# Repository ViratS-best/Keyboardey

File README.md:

Link: https://cad.onshape.com/documents/37fd5a85f79ebe20a6029276/w/db3c2ffc712adf7ef06de7c5/e/88f673a97a289337726580ef?renderMode=0&uiState=6ad8d7fe5b5abcf9bb015cb8

# Keyboardey

A weird keyboard CAD & Hardware design created for Half-Life.

## Overview

Keyboardey is a weird, funky, custom-designed keypad layout built entirely from scratch. This project was my second time ever using CAD, making it quite a large learning curve in learning how to design mechanical parts, shape custom keys, etc. I also designed a PCB to go along with this project!

# Cad

I also had to create a custom cutout extrude to position keys correctly!

PCB and Case on Onshape (This was when I didn't know that I would actually have to change key chapes, and cutout shape):

## Project Structure

```text
|── README.md
|── KEYBOARDEY.kicad__pcb
|── KEYBOARDEY.kicad__prl
|── KEYBOARDEY.kicad__pro
|── KEYBOARDEY.kicad__sch
|── Keyboardey.step
```

# PCB

I decided to not use a module microcontroller but rather build one myself:

Then I added the keyboard matrix:

Finished MCU schematic:

Routing & Placement:

# BoM

| Component / Service  | Description                           | Cost    |
| -------------------- | ------------------------------------- | ------- |
| PCB & Assembly       | Manufactured and assembled via JLCPCB | $29.08  |
| 3D Printing          | Case and custom keycaps (estimated)   | ~$4.25 |
| Kalih Choc Switches  | Low profile key switches for keys     | $8  |
| Shipping             | Shipping and handling                 | $31.55  |
| Total Estimated Cost |                                       | ~$72.88 |

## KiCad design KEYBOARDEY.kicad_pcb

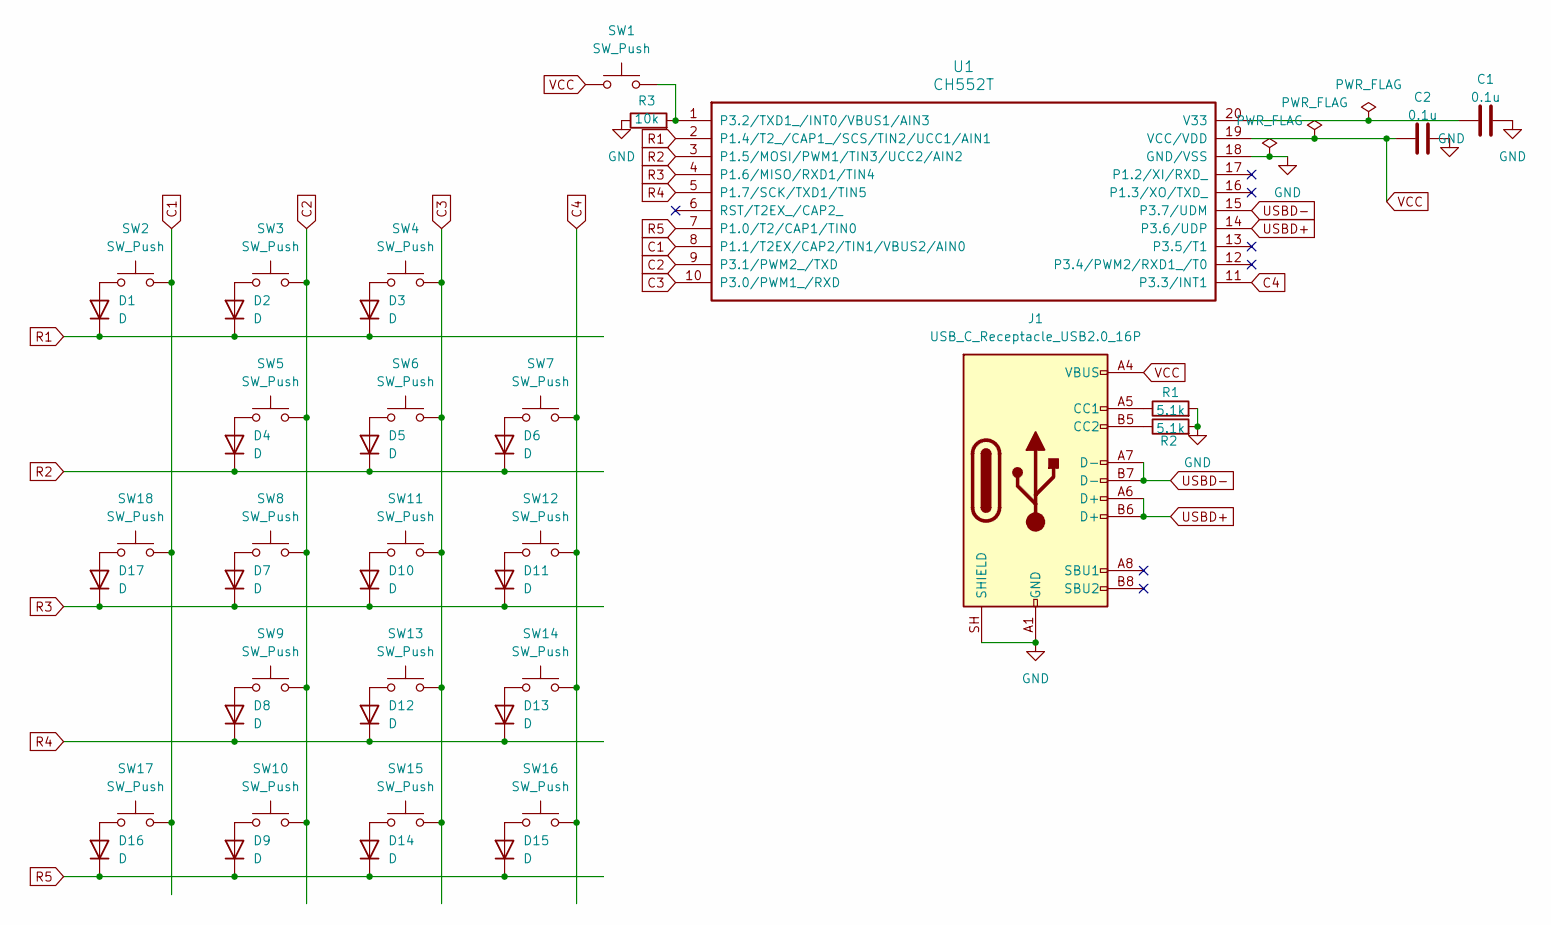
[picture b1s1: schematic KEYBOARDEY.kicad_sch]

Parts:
C1, C2: 0.1u; C_0402_1005Metric
D1, D2, D3, D4, D5, D6, D7, D8, D9, D10, D11, D12, D13, D14, D15, D16, D17: D; D_SOD-123
J1: USB_C_Receptacle_USB2.0_16P; USB_C_Receptacle_HRO_TYPE-C-31-M-12
R1, R2: 5.1k; R_0402_1005Metric
R3: 10k; R_0402_1005Metric
SW1: SW_Push; SW_Push_SPST_NO_Alps_SKRK
SW2, SW3, SW4, SW5, SW6, SW7, SW8, SW9, SW10, SW11, SW12, SW13, SW14, SW15, SW16, SW17, SW18: SW_Push; Kailh Choc Low-Profile Switches
U1: CH552T; TSSOP-20_4.4x6.5mm_P0.65mm

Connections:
C1: SW2.2, SW17.2, SW18.2, U1.8 (P1.1/T2EX/CAP2/TIN1/VBUS2/AIN0)
C2: SW3.2, SW5.2, SW8.2, SW9.2, SW10.2, U1.9 (P3.1/PWM2_/TXD)
C3: SW4.2, SW6.2, SW11.2, SW13.2, SW15.2, U1.10 (P3.0/PWM1_/RXD)
C4: SW7.2, SW12.2, SW14.2, SW16.2, U1.11 (P3.3/INT1)
GND: C1.2, C2.2, J1.A1 (GND), J1.A12 (GND), J1.B1 (GND), J1.B12 (GND), J1.SH (SHIELD), R1.2, R2.2, R3.1, U1.18 (GND/VSS)
unnamed: D1.2 (A), SW2.1
unnamed: D2.2 (A), SW3.1
unnamed: D3.2 (A), SW4.1
unnamed: D4.2 (A), SW5.1
unnamed: D5.2 (A), SW6.1
unnamed: D6.2 (A), SW7.1
unnamed: D7.2 (A), SW8.1
unnamed: D8.2 (A), SW9.1
unnamed: D9.2 (A), SW10.1
unnamed: D10.2 (A), SW11.1
unnamed: D11.2 (A), SW12.1
unnamed: D12.2 (A), SW13.1
unnamed: D13.2 (A), SW14.1
unnamed: D14.2 (A), SW15.1
unnamed: D15.2 (A), SW16.1
unnamed: D16.2 (A), SW17.1
unnamed: D17.2 (A), SW18.1
unnamed: J1.A5 (CC1), R1.1
unnamed: J1.B5 (CC2), R2.1
unnamed: R3.2, SW1.2, U1.1 (P3.2/TXD1_/INT0/VBUS1/AIN3)
unnamed: C1.1, U1.20 (V33)
R1: D1.1 (K), D2.1 (K), D3.1 (K), U1.2 (P1.4/T2_/CAP1_/SCS/TIN2/UCC1/AIN1)
R2: D4.1 (K), D5.1 (K), D6.1 (K), U1.3 (P1.5/MOSI/PWM1/TIN3/UCC2/AIN2)
R3: D7.1 (K), D10.1 (K), D11.1 (K), D17.1 (K), U1.4 (P1.6/MISO/RXD1/TIN4)
R4: D8.1 (K), D12.1 (K), D13.1 (K), U1.5 (P1.7/SCK/TXD1/TIN5)
R5: D9.1 (K), D14.1 (K), D15.1 (K), D16.1 (K), U1.7 (P1.0/T2/CAP1/TIN0)
USBD+: J1.A6 (D+), J1.B6 (D+), U1.14 (P3.6/UDP)
USBD-: J1.A7 (D-), J1.B7 (D-), U1.15 (P3.7/UDM)
VCC: C2.1, J1.A4 (VBUS), J1.A9 (VBUS), J1.B4 (VBUS), J1.B9 (VBUS), SW1.1, U1.19 (VCC/VDD)

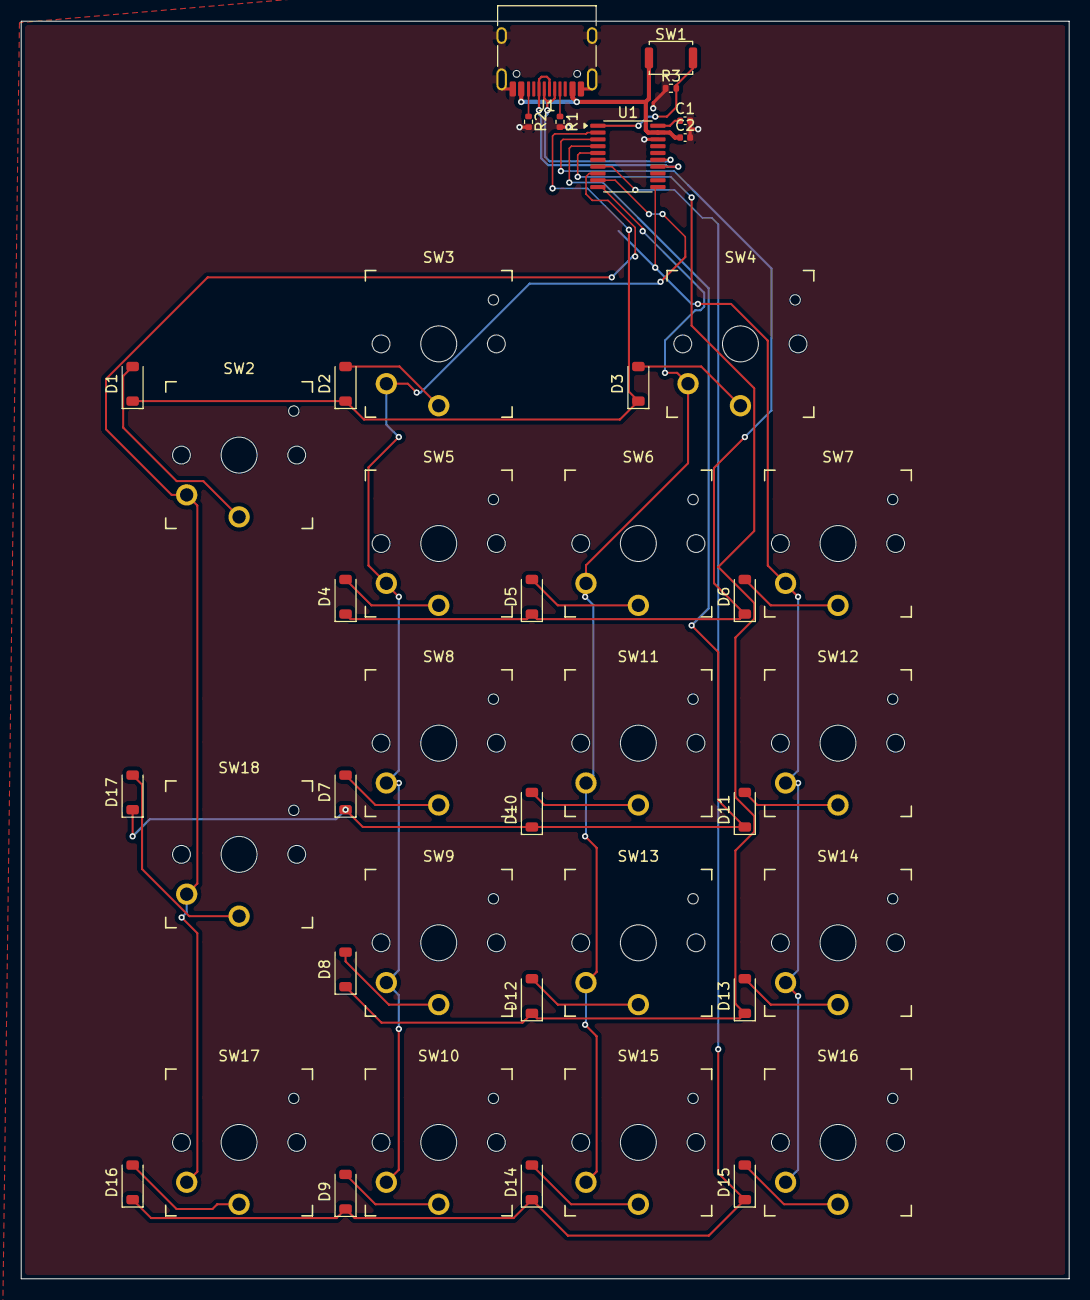
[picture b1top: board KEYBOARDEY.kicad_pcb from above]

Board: 2 copper layers, 100.0 x 120.0 mm, 42 parts (0 on the bottom side), 34 nets.

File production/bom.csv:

Designator,Footprint,Quantity,Value,LCSC Part #
"C1, C2",0402,2,0.1u,
"D1, D10, D11, D12, D13, D14, D15, D16, D17, D2, D3, D4, D5, D6, D7, D8, D9",D_SOD-123,17,D,
J1,USB_C_Receptacle_HRO_TYPE-C-31-M-12,1,USB_C_Receptacle_USB2.0_16P,
"R1, R2",0402,2,5.1k,
R3,0402,1,10k,
SW1,SW_Push_SPST_NO_Alps_SKRK,1,SW_Push,
"SW10, SW11, SW12, SW13, SW14, SW15, SW16, SW17, SW18, SW2, SW3, SW4, SW5, SW6, SW7, SW8, SW9",Kailh Choc Low-Profile Switches,17,SW_Push,
U1,TSSOP-20_4.4x6.5mm_P0.65mm,1,CH552T,
